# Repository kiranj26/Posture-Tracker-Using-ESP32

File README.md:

# Posture Tracker V2 — Product Grade Wearable

> **Branch:** `release/v2-product`  
> **Status:** In development  
> **V1 (MVP breadboard):** See [main branch](../../tree/main)

A product-grade evolution of the ESP32 posture tracker. V2 moves from a breadboard
prototype to a wearable device — custom PCB, LiPo battery, haptic motor, and a compact
shoulder-clip form factor small enough to wear all day.

**Hardware:** ESP32-S3-MINI-1 · MPU-6050 · DRV2605L + LRA · MAX98357A · 20mm speaker · 350mAh LiPo  
**Stack:** ESP-IDF 5.5.0 · PlatformIO · C only (no Arduino, no C++)  
**Target size:** 45×35×16mm (PCB + battery + clip)

---

## What's New in V2

| Feature | V1 | V2 |
|---|---|---|
| Alerts | Audio only | Haptic (early) + Audio (escalation) |
| MCU | ESP32 Dev Kit breakout | ESP32-S3-MINI-1 stamp module (built-in PCB antenna) |
| Power | USB only | 350mAh LiPo — 12–15 hr battery life |
| PCB | Breadboard + breakouts | Custom 2-layer PCB, all ICs direct |
| Speaker | 3W 4Ω (50mm, large) | 0.5W 8Ω (20mm, compact) |
| USB | Micro-USB | USB-C with proper CC resistors |
| Buttons | None | 2 buttons — recalibrate + snooze |
| Form factor | ~120×80mm breadboard | 45×35×16mm shoulder clip |

---

## Alert UX — Layered Haptic + Audio

The key design principle: **haptics for early alerts, audio only for escalation.**

| Time / State | Haptic | Audio |
|---|---|---|
| 10° for 3s — WARNING entry | Single tap | Silent |
| WARNING sustained | Double tap | Silent |
| 20° for 5s — BAD entry | Strong double tap | Double beep |
| BAD +8s | Triple pulse | Double beep |
| BAD +16s | Triple pulse | Double beep |
| BAD +24s onwards | Triple pulse | "Sit up straight" — repeats every 8s |
| Posture corrected | Long reward pulse | "Thank you good work" |
| 30s good streak | Gentle pulse | Silent |

SW2 (snooze button) mutes all audio for 10 minutes while haptics continue —
for meetings, calls, or quiet environments.

---

## Hardware

### Component List

| Component | Part | Purpose |
|---|---|---|
| ESP32-S3-MINI-1 | Espressif | MCU — dual core, BLE 5.0, native USB, built-in PCB antenna |
| MPU-6050 | InvenSense | 6-axis IMU — pitch/roll angle sensing |
| DRV2605L | Texas Instruments | Haptic driver — 123 built-in LRA waveforms |
| Z10SC2B LRA | Jinlong | 10mm linear resonant actuator — sharp haptic taps |
| MAX98357A | Maxim | I2S Class D amplifier — voice clips + tones |
| CMS-2009-SMT-TR | CUI Devices | 20mm 8Ω 0.5W speaker |
| MCP73831 | Microchip | LiPo charging IC — 100mA from USB-C |
| AP2112K-3.3 | Diodes Inc | 600mA LDO regulator — 3.3V rail |
| USBLC6-2SC6 | STMicro | USB ESD protection on D+/D- lines |
| 350mAh LiPo | Generic | Battery — 12–15 hour runtime |
| USB-C (HRO TYPE-C-31-M-12) | HRO | Charging + programming port, both-orientation USB 2.0 |

### Pin Assignment

| Signal | GPIO | Notes |
|---|---|---|
| I2C SDA | 8 | MPU-6050 + DRV2605L shared (GPIO21/22 do not exist on ESP32-S3) |
| I2C SCL | 9 | MPU-6050 + DRV2605L shared |
| I2S BCLK | 26 | MAX98357A |
| I2S WS | 25 | MAX98357A |
| I2S DOUT | 27 | MAX98357A |
| SW1 BOOT/CAL | 0 | Recalibrate / ESP32 boot |
| SW2 SNOOZE | 35 | 10-min snooze / mute toggle |
| SW3 RESET | EN pin | Hardware reset button |
| VBAT SENSE | 34 | ADC — battery voltage monitor |
| AUDIO MUTE | 48 | MAX98357A SD_MODE |
| USB D+ | 20 | Via USBLC6-2SC6 ESD protection |
| USB D- | 19 | Via USBLC6-2SC6 ESD protection |

---

## Architecture

### Three FreeRTOS tasks (V1) + Two new tasks (V2)

| Task | Core | Priority | Purpose |
|---|---|---|---|
| task_read_imu | 0 | 5 | IMU read every 100ms with light sleep |
| task_posture_fsm | 0 | 4 | State machine — unchanged from V1 |
| task_audio | 1 | 3 | Audio + haptic dispatch |
| task_buttons | 0 | 2 | Debounced button events |
| task_power | 0 | 1 | Battery monitor every 60s |

### New modules vs V1

```
NEW:      haptic.c    — DRV2605L I2C driver, waveform playback (non-blocking)
NEW:      power.c     — battery ADC, low-battery warning, deep sleep entry
NEW:      buttons.c   — debounced GPIO, short/long press detection

UNCHANGED: mpu6050.c  — I2C driver, atan2 angle math, EMA filter
UNCHANGED: posture_fsm.c — state machine logic (only alert commands change)
MODIFIED:  audio.c    — adds haptic command dispatch alongside audio
MODIFIED:  main.c     — init order adds haptic, power, buttons
```

---

## Power System

```
USB-C (5V) → Polyfuse → MCP73831 LiPo charger → 350mAh LiPo
                                                        ↓
                                                  AP2112K LDO
                                                        ↓
                                                    3.3V rail → all ICs
```

**Battery life estimate:**
- Active draw (IMU reading, no alerts): ~6mA average with light sleep
- 350mAh ÷ 6mA = ~58 hours theoretical
- Real world (audio bursts, haptic, occasional BLE): **12–15 hours**

**Low battery handling:**
- < 3.5V → warning beep + haptic
- < 3.3V → shutdown tone + deep sleep

---

## Form Factor

```
Assembled dimensions:
  PCB alone:        45 × 35 × 1.6mm
  PCB + battery:    45 × 35 × 8mm
  With clip:        45 × 38 × 16mm   ← final wearable size

Comparable to a car key fob.
Clips onto shirt collar, bra strap, or epaulette.
LRA motor faces the body for best haptic transmission.
Speaker grille faces outward.
USB-C and buttons accessible on edges.
```

---

## Development Phases

| Phase | Description | Status | Hardware |
|---|---|---|---|
| 7 | Haptic validation on breadboard (DRV2605L + LRA) | ⏳ Next | 📦 Parts ordered |
| 8 | Speaker swap validation (20mm 8Ω 1W) | ⏳ Next | 📦 Parts ordered |
| 9 | Battery system validation (MCP73831 + LiPo) | ⏳ Pending | 📦 Parts ordered |
| 10 | PCB V2 schematic + layout + fabrication (JLCPCB) | 🔄 PCB complete — awaiting order | Schematic ✅ ERC clean. Layout ✅ fully routed. DRC ✅ 0 errors, 0 unconnected, 2 cosmetic silk warnings. Gerbers ✅ `hardware/pcb/v2/`. JLCPCB order ⏳ pending. |
| 11 | Full integration + enclosure (3D printed clip) | ⏳ Pending | 🛒 Order after Phase 10 |

---

## Branch Structure

```
main                        ← V1 MVP (public, breadboard, complete)
  └── release/v2-product    ← this branch — all V2 work
        └── feature/haptics
        └── feature/speaker-swap
        └── feature/power-system
        └── feature/pcb-v2
        └── feature/enclosure
```

---

## PCB Layout — Complete

### Design decisions locked
- **2-layer board** — F.Cu for all signal and power traces, B.Cu solid GND copper pour
- **Trace widths (IPC-2221 verified, 1oz copper, 10°C rise)** — VBUS/VBUS_FUSED: 0.4mm, +3V3/VBAT/audio/motor: 0.3mm, all signals: 0.2mm
- **Net classes** — HighCurrent (0.4mm), Power (0.3mm), Audio (0.3mm), Motor (0.3mm), USB_Diff (0.2mm impedance-controlled), Default (0.2mm)
- **Via spec** — 0.8mm outer / 0.4mm drill (JLCPCB standard rule compliant)
- **Board size** — ~47.6 × 28.3mm (fits 45×35×16mm wearable form factor with battery)
- **Connectors** — J1: USB-C (HRO TYPE-C-31-M-12), J2: JST PH 2mm (battery), J3: Molex PicoBlade 53261-0271 (LRA haptic), LS1: Molex PicoBlade 53261-0271 (speaker)

### Routing status
| Net group | Connections | Status |
|---|---|---|
| GND | ~72 | ✅ B.Cu + F.Cu copper pour, stitching vias placed |
| +3V3 | 23 | ✅ Routed |
| VBAT | 7 | ✅ Routed |
| VBUS / VBUS_FUSED | 4 | ✅ Routed |
| I2C (SDA/SCL) | 6 | ✅ Routed |
| USB_DP / USB_DM | 8 | ✅ Routed |
| I2S (BCLK/WS/DOUT) | 3 | ✅ Routed |
| Signals + buttons | ~31 | ✅ Routed |

**Final DRC (2026-06-09):** 0 errors, 0 unconnected, 2 cosmetic silk warnings (U1 silkscreen clips board edge — JLCPCB trims automatically).

### File locations
```
hardware/
├── kicad/posture_tracker_v2/
│   └── posture_tracker_v2/    ← KiCad source (schematic + PCB + project files)
│       └── reports/           ← DRC.rpt, ERC.rpt
├── schematics/                ← Exported schematic PDF (posture_tracker_v2_v2.pdf)
├── pcb/
│   └── v2/
│       ├── gerbers/           ← 12 Gerber + drill files (canonical fab outputs)
│       └── posture_tracker_v2_gerbers.zip  ← upload this to JLCPCB
├── bom/                       ← Bill of materials
└── datasheets/                ← Component datasheets
```

---

## Hardware Visuals

### PCB — 3D View

### PCB — Top Layer

### PCB — Bottom Layer

### PCB — Combined

### Schematic

> Full schematic PDF: [hardware/schematics/posture_tracker_v2_v2.pdf](hardware/schematics/posture_tracker_v2_v2.pdf)

> PCB layer PDFs (vector): [Top](hardware/assets/pcb_v2_top_layer.pdf) · [Bottom](hardware/assets/pcb_v2_bottom_layer.pdf) · [Combined](hardware/assets/pcb_v2_combined.pdf)

---

## Reference Docs

- [CLAUDE.md](CLAUDE.md) — full V2 architecture, component decisions, hard rules, PCB design reference
- [PHASES.md](PHASES.md) — V2 phase build guide (phases 7–11)
- [hardware/schematics/SCHEMATIC_GUIDE.md](hardware/schematics/SCHEMATIC_GUIDE.md) — full reasoning for every schematic block

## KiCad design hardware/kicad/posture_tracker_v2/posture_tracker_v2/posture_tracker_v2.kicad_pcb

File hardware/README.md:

# Hardware

All hardware design files for Posture Tracker V2.

## Folder Structure

```
hardware/
├── datasheets/    ← PDF datasheets for every component on the BOM
├── kicad/         ← KiCad project files (schematic + PCB)
├── schematics/    ← Exported schematic PDFs per revision
├── pcb/           ← KiCad PCB layout + Gerber exports for JLCPCB
├── enclosure/     ← 3D printable clip files (STL + source)
└── bom/           ← Master BOM and JLCPCB-formatted exports
```

## Current Status

| Folder | Status | Notes |
|---|---|---|
| datasheets | ✅ Done | All component datasheets present — see datasheets/README.md |
| kicad | ✅ Complete | Schematic (ERC clean) + PCB layout (DRC clean) + Gerbers exported |
| schematics | ✅ Done | Exported PDF at `schematics/posture_tracker_v2_v2.pdf` |
| pcb | ✅ Gerbers ready | `pcb/v2/gerbers/` — 12 files + ZIP ready for JLCPCB upload |
| enclosure | ⬜ Not started | Waiting on PCB prototypes received (Phase 10) |
| bom | ✅ Master BOM started | Update as parts ordered for Phase 10 |

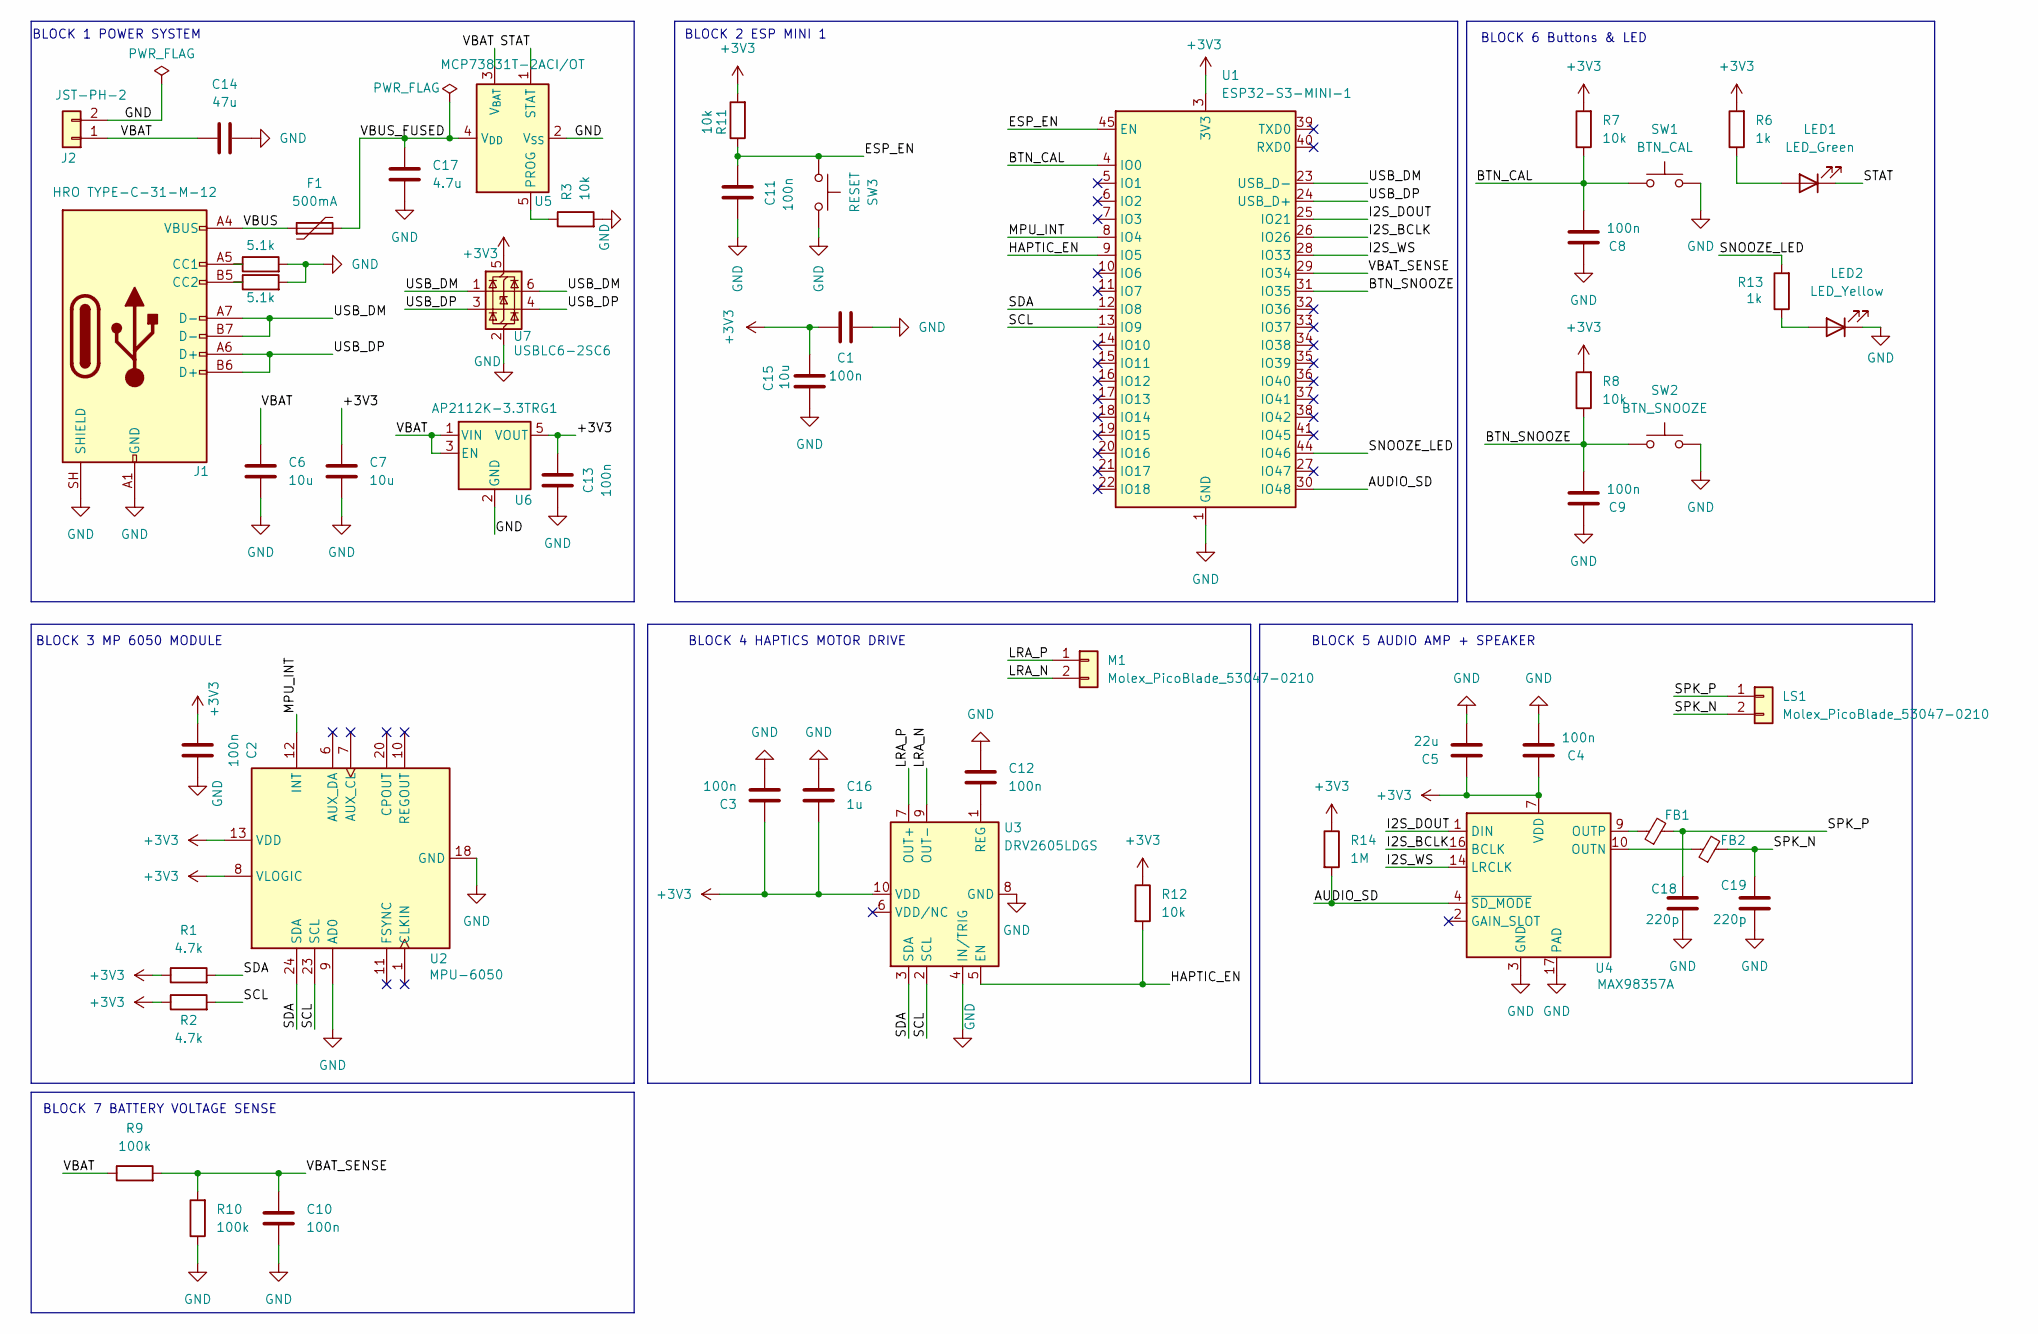
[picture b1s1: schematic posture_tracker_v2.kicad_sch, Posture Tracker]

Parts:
C1, C2, C3, C4, C8, C9, C10, C11, C12, C13: 100n; C_0402_1005Metric
C5: 22u; C_0805_2012Metric
C6, C7, C15: 10u; C_0805_2012Metric
C14: 47u; C_0805_2012Metric
C16: 1u; C_0402_1005Metric
C17: 4.7u; C_0402_1005Metric
C18, C19: 220p; C_0805_2012Metric
F1: 500mA; Fuse_0805_2012Metric
FB1, FB2: FerriteBead_Small; L_0402_1005Metric
J1: HRO TYPE-C-31-M-12; USB_C_Receptacle_HRO_TYPE-C-31-M-12
J2: JST-PH-2; JST_PH_S2B-PH-K_1x02_P2.00mm_Horizontal
LED1: LED_Green; LED_0805_2012Metric
LED2: LED_Yellow; LED_0805_2012Metric
LS1: Molex_PicoBlade_53047-0210; Molex_PicoBlade_53047-0210_1x02_P1.25mm_Vertical
M1: Molex_PicoBlade_53047-0210; Molex_PicoBlade_53047-0210_1x02_P1.25mm_Vertical
R1, R2: 4.7k; R_0402_1005Metric
R3, R7, R8, R11, R12: 10k; R_0402_1005Metric
R4, R5: 5.1k; R_0402_1005Metric
R6, R13: 1k; R_0402_1005Metric
R9, R10: 100k; R_0402_1005Metric
R14: 1M; R_0402_1005Metric
SW1: BTN_CAL; SW_SKRPABE010
SW2: BTN_SNOOZE; SW_SKRPABE010
SW3: RESET; SW_SKRPABE010
U1: ESP32-S3-MINI-1; ESP32-S2-MINI-1
U2: MPU-6050; InvenSense_QFN-24_4x4mm_P0.5mm
U3: DRV2605LDGS; TSSOP-10_3x3mm_P0.5mm
U4: MAX98357A; TQFN-16-1EP_3x3mm_P0.5mm_EP1.23x1.23mm
U5: MCP73831T-2ACI/OT; SOT-23-5
U6: AP2112K-3.3TRG1; SOT-23-5
U7: USBLC6-2SC6; SOT-23-6

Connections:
+3V3: C1.1, C2.1, C3.1, C4.1, C5.1, C7.1, C13.2, C15.2, C16.2, R1.1, R2.1, R6.2, R7.2, R8.2, R11.2, R12.1, R14.1, U1.3 (3V3), U2.8 (VLOGIC), U2.13 (VDD), U3.10 (VDD), U4.7 (VDD), U4.8 (VDD), U6.5 (VOUT), U7.5 (VBUS)
/AUDIO_SD: R14.2, U1.30 (IO48), U4.4 (~SD_MODE)
/BTN_CAL: C8.2, R7.1, SW1.1, U1.4 (IO0)
/BTN_SNOOZE: C9.2, R8.1, SW2.1, U1.31 (IO35)
/ESP_EN: C11.2, R11.1, SW3.1, U1.45 (EN)
/HAPTIC_EN: R12.2, U1.9 (IO5), U3.5 (EN)
/I2S_BCLK: U1.26 (IO26), U4.16 (BCLK)
/I2S_DOUT: U1.25 (IO21), U4.1 (DIN)
/I2S_WS: U1.28 (IO33), U4.14 (LRCLK)
/LRA_N: M1.2, U3.9 (OUT-)
/LRA_P: M1.1, U3.7 (OUT+)
/MPU_INT: U1.8 (IO4), U2.12 (INT)
/SCL: R2.2, U1.13 (IO9), U2.23 (SCL), U3.2 (SCL)
/SDA: R1.2, U1.12 (IO8), U2.24 (SDA), U3.3 (SDA)
/SNOOZE_LED: R13.2, U1.44 (IO46)
/SPK_N: C19.2, FB2.2, LS1.2
/SPK_P: C18.2, FB1.2, LS1.1
/STAT: LED1.1 (K), U5.1 (STAT)
/USB_DM: J1.A7 (D-), J1.B7 (D-), U1.23 (USB_D-), U7.1 (I/O1), U7.6 (I/O1)
/USB_DP: J1.A6 (D+), J1.B6 (D+), U1.24 (USB_D+), U7.3 (I/O2), U7.4 (I/O2)
/VBAT: C6.1, C14.1, J2.1, R9.1, U5.3 (V_{BAT}), U6.1 (VIN), U6.3 (EN)
/VBAT_SENSE: C10.1, R9.2, R10.2, U1.29 (IO34)
/VBUS: F1.1, J1.A4 (VBUS), J1.A9 (VBUS), J1.B4 (VBUS), J1.B9 (VBUS)
/VBUS_FUSED: C17.2, F1.2, U5.4 (V_{DD})
GND: C1.2, C2.2, C3.2, C4.2, C5.2, C6.2, C7.2, C8.1, C9.1, C10.2, C11.1, C12.2, C13.1, C14.2, C15.1, C16.1, C17.1, C18.1, C19.1, J1.A1 (GND), J1.A12 (GND), J1.B1 (GND), J1.B12 (GND), J1.SH (SHIELD), J2.2, LED2.1 (K), R3.2, R4.2, R5.2, R10.1, SW1.2, SW2.2, SW3.2, U1.1 (GND), U1.2 (GND), U1.42 (GND), U1.43 (GND), U1.46 (GND), U1.47 (GND), U1.48 (GND), U1.49 (GND), U1.50 (GND), U1.51 (GND), U1.52 (GND), U1.53 (GND), U1.54 (GND), U1.55 (GND), U1.56 (GND), U1.57 (GND), U1.58 (GND), U1.59 (GND), U1.60 (GND), U1.61 (GND), U1.62 (GND), U1.63 (GND), U1.64 (GND), U1.65 (GND), U2.9 (AD0), U2.18 (GND), U3.4 (IN/TRIG), U3.8 (GND), U4.3 (GND), U4.11 (GND), U4.15 (GND), U4.17 (PAD), U5.2 (V_{SS}), U6.2 (GND), U7.2 (GND)
unnamed: J1.A5 (CC1), R4.1
unnamed: J1.B5 (CC2), R5.1
unnamed: LED1.2 (A), R6.1
unnamed: LED2.2 (A), R13.1
unnamed: C12.1, U3.1 (REG)
unnamed: FB2.1, U4.10 (OUTN)
unnamed: FB1.1, U4.9 (OUTP)
unnamed: R3.1, U5.5 (PROG)

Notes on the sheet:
BLOCK 2 ESP MINI 1
BLOCK 4 HAPTICS MOTOR DRIVE
BLOCK 1 POWER SYSTEM
BLOCK 6 Buttons & LED
BLOCK 7 BATTERY VOLTAGE SENSE
BLOCK 3 MP 6050 MODULE
BLOCK 5 AUDIO AMP + SPEAKER

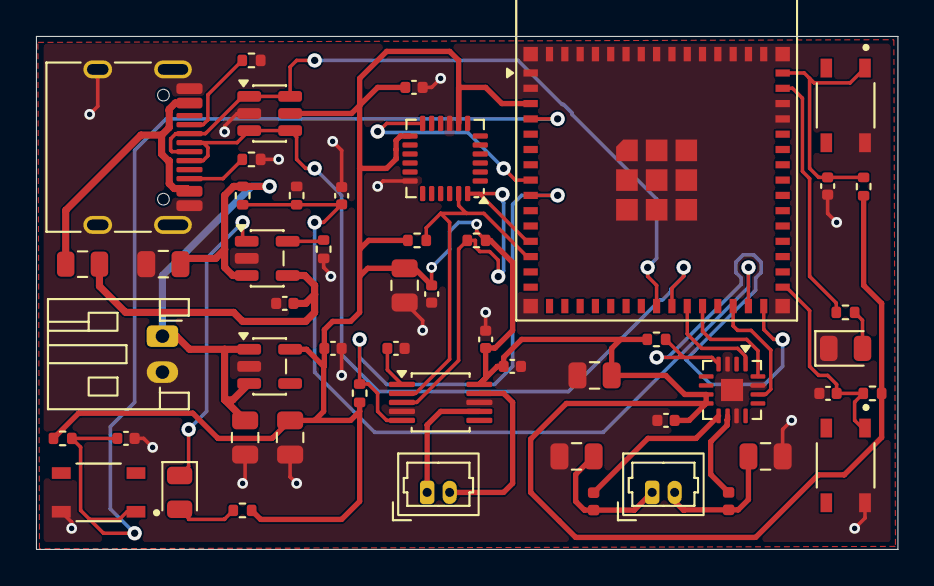
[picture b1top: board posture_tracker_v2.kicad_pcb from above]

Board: 2 copper layers, 47.9 x 28.5 mm, 52 parts (0 on the bottom side), 33 nets.

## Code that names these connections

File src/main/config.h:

#pragma once

// ── I2C (MPU-6050) ────────────────────────────────────────────────────────
#define I2C_MASTER_PORT         I2C_NUM_0
#define I2C_MASTER_SDA_IO       21
#define I2C_MASTER_SCL_IO       22
#define I2C_MASTER_FREQ_HZ      400000      // 400kHz Fast Mode
#define I2C_TIMEOUT_MS          100

// ── MPU-6050 registers ────────────────────────────────────────────────────
#define MPU6050_ADDR            0x68
#define MPU_REG_PWR_MGMT_1      0x6B
#define MPU_REG_WHO_AM_I        0x75
#define MPU_REG_SMPLRT_DIV      0x19
#define MPU_REG_CONFIG          0x1A
#define MPU_REG_ACCEL_CONFIG    0x1C
#define MPU_REG_GYRO_CONFIG     0x1B
#define MPU_REG_ACCEL_XOUT_H    0x3B
#define MPU_WHO_AM_I_RESPONSE   0x68
#define MPU_ACCEL_SENSITIVITY   16384.0f    // LSB/g for ±2g range

// ── I2S (MAX98357A) ───────────────────────────────────────────────────────
#define I2S_PORT_NUM            I2S_NUM_0
#define I2S_BCLK_IO             26
#define I2S_WS_IO               25
#define I2S_DOUT_IO             27
#define I2S_SAMPLE_RATE_HZ      44100
#define WAV_SAMPLE_RATE_HZ      16000       // sit_up.wav recorded at 16kHz
#define I2S_BITS_PER_SAMPLE     16
#define I2S_DMA_BUF_COUNT       8
#define I2S_DMA_BUF_LEN_SMPLS  512

// ── IMU sampling ─────────────────────────────────────────────────────────
#define IMU_SAMPLE_RATE_MS      100         // Task A loop delay (ms)
#define LPF_ALPHA               0.15f       // EMA coefficient — lower = smoother

// ── Calibration ───────────────────────────────────────────────────────────
#define CAL_TOTAL_SAMPLES       30          // 3 seconds at 100ms per sample
#define CAL_DISCARD_SAMPLES     5           // Discard first 500ms (filter settle)
#define CAL_MAX_STDDEV_DEG      5.0f        // Reject cal if stddev exceeds this
#define CAL_VALID_SAMPLES       (CAL_TOTAL_SAMPLES - CAL_DISCARD_SAMPLES)

// ── Posture thresholds ────────────────────────────────────────────────────
#define WARN_THRESH_DEG         10.0f       // ° from baseline → WARNING state
#define BAD_THRESH_DEG          20.0f       // ° from baseline → BAD state
#define JUMP_FILTER_DEG         60.0f       // ° — discard violent movement sample

// ── State machine timings ─────────────────────────────────────────────────
#define WARN_GRACE_MS           3000        // ms above WARN_THRESH before alert fires
#define BAD_GRACE_MS            5000        // ms above BAD_THRESH before BAD fires
#define RESET_COOLDOWN_MS       2000        // ms in RESET before returning to GOOD
#define REPEAT_ALERT_MS         8000        // ms between repeated BAD alerts
#define ESCALATION_CAP          3           // beep cycles before switching to voice clip
#define GOOD_STREAK_REWARD_MS   30000       // ms of GOOD before reward chime (30s)

// ── Audio volumes (0.0 – 1.0) ─────────────────────────────────────────────
#define VOL_WARNING             0.35f
#define VOL_BAD                 0.80f
#define VOL_CHIME               0.55f
#define VOL_VOICE               0.90f
#define VOL_BOOT                0.50f
#define TONE_FADE_MS            10          // Fade in/out ms — prevents speaker click

// ── FreeRTOS ─────────────────────────────────────────────────────────────
#define AUDIO_QUEUE_DEPTH       5
#define TASK_STACK_IMU          4096
#define TASK_STACK_FSM          4096
#define TASK_STACK_AUDIO        8192
#define TASK_PRIO_IMU           5
#define TASK_PRIO_FSM           4
#define TASK_PRIO_AUDIO         3
#define TASK_CORE_IMU           0
#define TASK_CORE_FSM           0
#define TASK_CORE_AUDIO         1
#define MUTEX_TIMEOUT_MS        5           // Max ms to wait for imu_mutex before skip

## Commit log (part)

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2026-04-26 README: add video demo placeholder at top
2026-04-26 Change demo video link in README.md
    Updated demo video link in README.
2026-04-26 README: add demo walkthrough below video
2026-04-26 docs: mark Phase 6 endurance testing complete, fix README structure
2026-04-26 Add future PCB enclosure section to README
    Added a section for future PCB enclosure with an image.
2026-04-26 V2: add CLAUDE_V2.md and README_V2.md — full product architecture
2026-04-26 V2: add PHASES_V2.md — full phase build guide for phases 7-11
2026-04-26 V2: remove Elegoo sensor kit folder from datasheets — not relevant to V2
